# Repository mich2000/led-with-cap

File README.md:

# led-with-cap

## Upload project to eurocircuits/jlcpcb

* make sure to include drill files, important for usb-c connector.

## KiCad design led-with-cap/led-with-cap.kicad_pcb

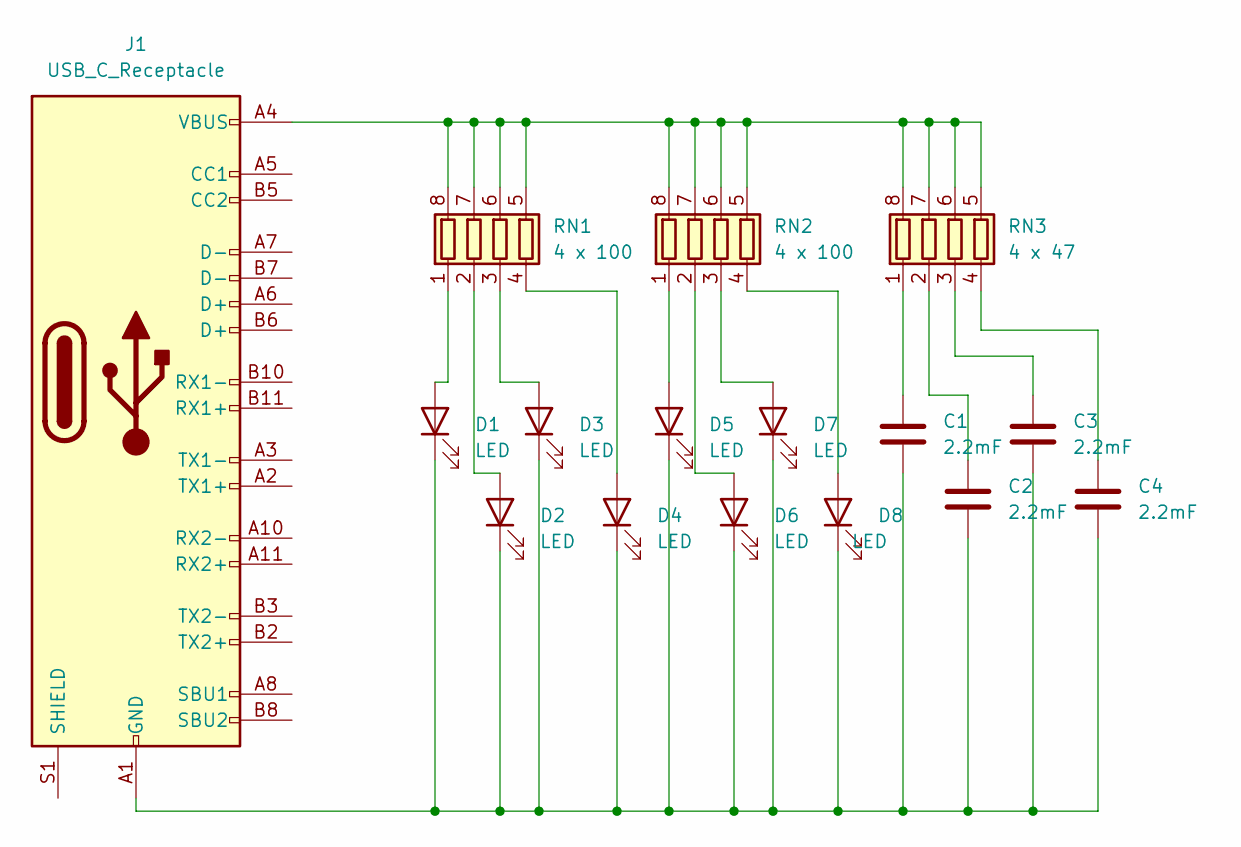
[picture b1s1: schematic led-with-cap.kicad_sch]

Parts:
C1, C2, C3, C4: 2.2mF; CP_Elec_12.5
D1, D2, D3, D4, D5, D6, D7, D8: LED; LED_1206_3216Metric_Pad1.42x1.75mm_HandSolder
J1: USB_C_Receptacle; USB_C_Receptacle_Amphenol_12401548E4-2A
RN1, RN2: 4 x 100; R_Array_Convex_4x1206
RN3: 4 x 47; R_Array_Convex_4x1206

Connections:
unnamed: C1.1, RN3.1 (R1.1)
unnamed: C1.2, C2.2, C3.2, C4.2, D1.1 (K), D2.1 (K), D3.1 (K), D4.1 (K), D5.1 (K), D6.1 (K), D7.1 (K), D8.1 (K), J1.A1 (GND), J1.A12 (GND), J1.B1 (GND), J1.B12 (GND)
unnamed: C2.1, RN3.2 (R2.1)
unnamed: C3.1, RN3.3 (R3.1)
unnamed: C4.1, RN3.4 (R4.1)
unnamed: D1.2 (A), RN1.1 (R1.1)
unnamed: D2.2 (A), RN1.2 (R2.1)
unnamed: D3.2 (A), RN1.3 (R3.1)
unnamed: D4.2 (A), RN1.4 (R4.1)
unnamed: D5.2 (A), RN2.1 (R1.1)
unnamed: D6.2 (A), RN2.2 (R2.1)
unnamed: D7.2 (A), RN2.3 (R3.1)
unnamed: D8.2 (A), RN2.4 (R4.1)
unnamed: J1.A4 (VBUS), J1.A9 (VBUS), J1.B4 (VBUS), J1.B9 (VBUS), RN1.5 (R4.2), RN1.6 (R3.2), RN1.7 (R2.2), RN1.8 (R1.2), RN2.5 (R4.2), RN2.6 (R3.2), RN2.7 (R2.2), RN2.8 (R1.2), RN3.5 (R4.2), RN3.6 (R3.2), RN3.7 (R2.2), RN3.8 (R1.2)

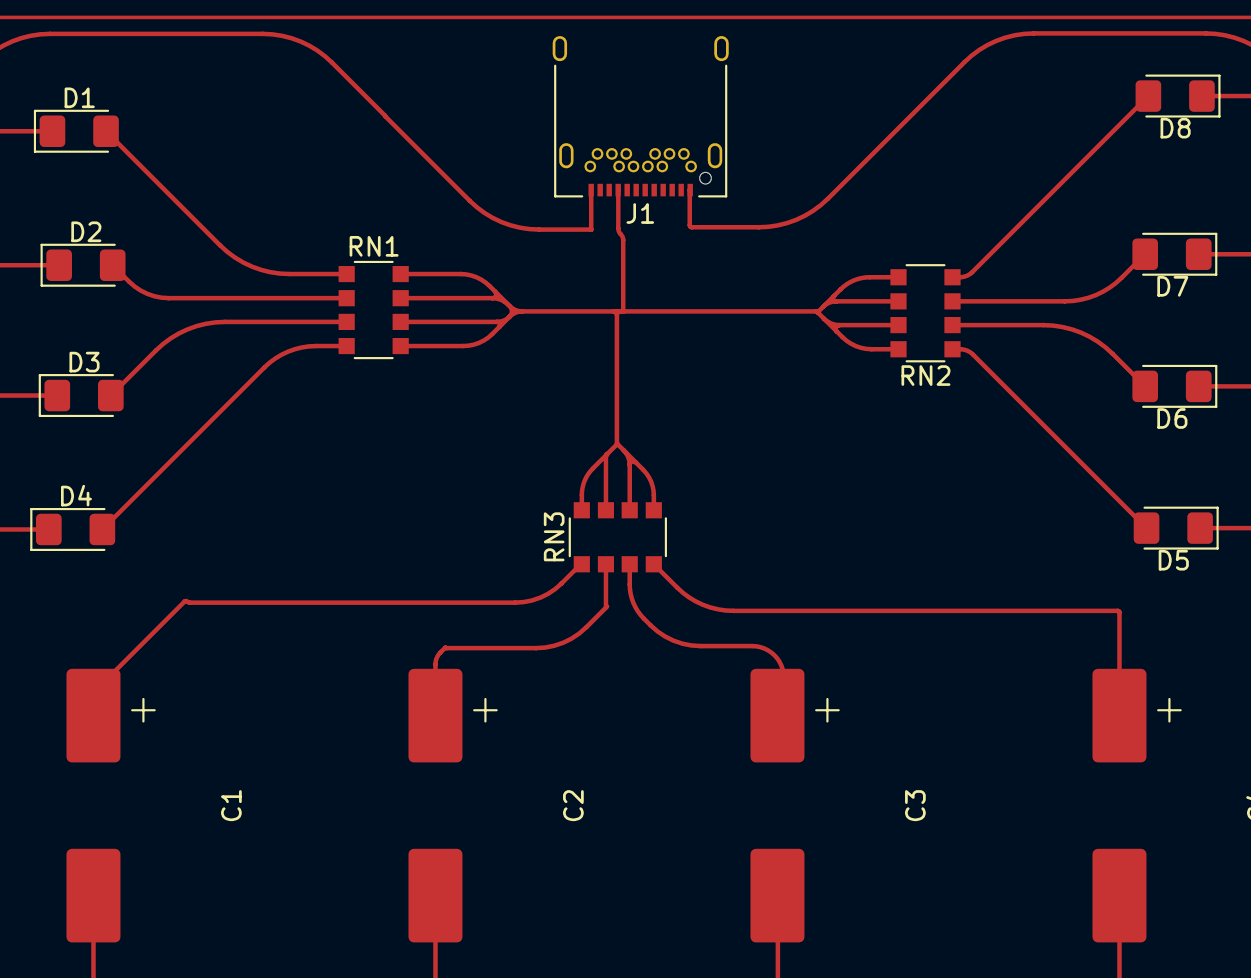
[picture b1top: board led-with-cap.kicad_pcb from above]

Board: 2 copper layers, 16 parts (0 on the bottom side), 14 nets.
